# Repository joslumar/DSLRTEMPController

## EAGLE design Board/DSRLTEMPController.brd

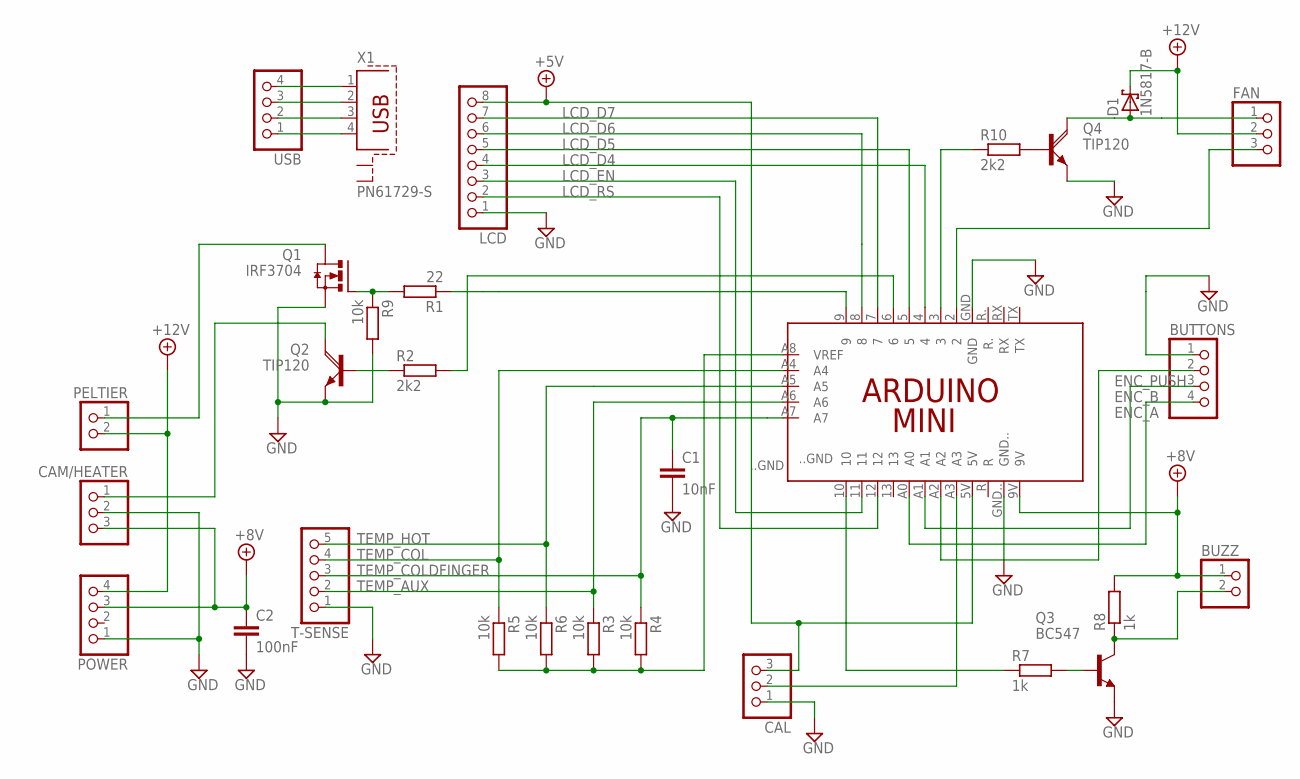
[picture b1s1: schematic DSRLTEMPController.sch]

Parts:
BUTTONS: PINHD-1X4; 1X04
BUZZ: PINHD-1X2; 1X02
C1: 10nF; C025-024X044
C2: 100nF; C025_050-025X075
CAL: PINHD-1X3; 1X03
CAM/HEATER: PINHD-1X3/90; 1X03/90
D1: 1N5817-B; DO41-7.6
FAN: PINHD-1X3/90; 1X03/90
LCD: PINHD-1X8; 1X08
PCB1: ARDUINO_MINI
PELTIER: PINHD-1X2/90; 1X02/90
POWER: PINHD-1X4/90; 1X04/90
Q1: IRF3704; TO220AH
Q2, Q4: TIP120; TO220AH
Q3: BC547; TO92
R1: 22; 0207/7
R2, R10: 2k2; 0207/7
R3, R4, R5, R6, R9: 10k; 0207/7
R7, R8: 1k; 0207/7
T-SENSE: PINHD-1X5; 1X05
USB: PINHD-1X4; 1X04
X1: PN61729-S

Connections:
+5V: CAL.3, LCD.8, PCB1.5V
+8V: BUZZ.1, C2.1, CAM/HEATER.3, PCB1.9V, POWER.3, R8.2
+12V: D1.C, FAN.2, PELTIER.2, POWER.4
ENC_A: BUTTONS.4, PCB1.A0
ENC_B: BUTTONS.3, PCB1.A1
ENC_PUSH: BUTTONS.2, PCB1.A2
GND: BUTTONS.1, C1.2, C2.2, CAL.1, CAM/HEATER.2, LCD.1, PCB1.GND, PCB1.GND.., POWER.1, Q1.E (S), Q2.E, Q3.1 (E), Q4.E, R9.2, T-SENSE.1
LCD_D4: LCD.5, PCB1.5
LCD_D5: LCD.4, PCB1.4
LCD_D6: PCB1.3, R10.1
LCD_D7: FAN.3, PCB1.2
LCD_EN: LCD.3, PCB1.11
LCD_RS: LCD.2, PCB1.12
unnamed: Q2.B, R2.1
unnamed: PCB1.9, R1.1
unnamed: PCB1.6, R2.2
unnamed: Q1.B (G), R1.2, R9.1
unnamed: CAM/HEATER.1, Q2.C
unnamed: PELTIER.1, Q1.C (D)
unnamed: PCB1.10, R7.1
unnamed: BUZZ.2, Q3.3 (C), R8.1
unnamed: Q3.2 (B), R7.2
unnamed: LCD.6, PCB1.8
unnamed: LCD.7, PCB1.7
unnamed: Q4.B, R10.2
unnamed: USB.4, X1.1
unnamed: D1.A, FAN.1, Q4.C
unnamed: USB.3, X1.2
unnamed: USB.2, X1.3
unnamed: USB.1, X1.4
unnamed: CAL.2, PCB1.A3
TEMP_AUX: PCB1.A6, R3.1, T-SENSE.2
TEMP_COL: PCB1.A4, R5.1, T-SENSE.4
TEMP_COLDFINGER: C1.1, PCB1.A7, R4.1, T-SENSE.3
TEMP_HOT: PCB1.A5, R6.1, T-SENSE.5
VREF: PCB1.A8 (VREF), R3.2, R4.2, R5.2, R6.2

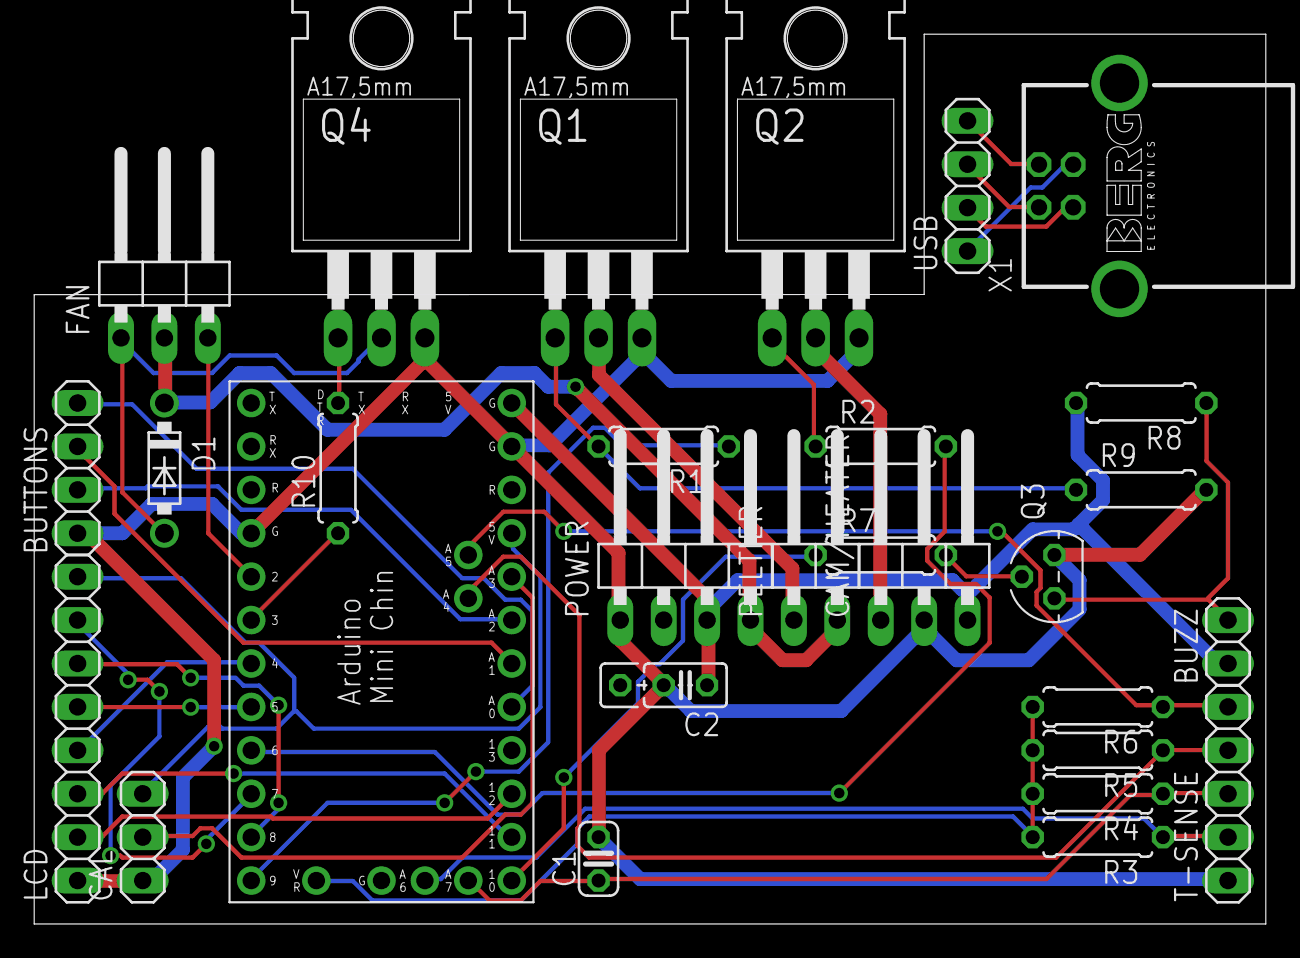
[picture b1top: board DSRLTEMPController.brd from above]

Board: 2 copper layers, 72.1 x 52.1 mm, 29 parts (0 on the bottom side), 36 nets.

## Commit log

2017-05-20 First
2017-05-20 new file: Board/DSRLTEMPController.brd new file: Board/DSRLTEMPController.sch
2017-05-20 renamed: DSLRTEMPController_v1_4_2.ino -> DSLRTEMPController.ino
2018-02-19 Cosmetic source changes
